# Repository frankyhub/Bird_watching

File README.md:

<div align="center">

|[:skull:ISSUE](https://github.com/frankyhub/Bird_watching/issues?q=is%3Aissue)|[:speech_balloon: Forum /Discussion](https://github.com/frankyhub/Bird_watching/discussions)|[:grey_question:WiKi](https://github.com/frankyhub/Bird_watching/wiki)||
|--|--|--|--|
| | | | |
<a href="https://github.com/frankyhub/Bird_watching/issues">|<a href="https://github.com/frankyhub/Bird_watching/discussions">|<a href="https://github.com/frankyhub/Bird_watching/releases">||
|| <a href="https://github.com/frankyhub/Bird_watching/pulse" alt="Activity">| <a href="https://github.com/frankyhub/Bird_watching/graphs/traffic">  |<a href="https://github.com/frankyhub?tab=stars"> ||

</div>

### Nach einer Idee von [Alex Kutschera](https://github.com/vektorious)

# Story
Die Blaumeise und die Kohlmeise gehören zu den häufigsten Meisenarten in Deutschland. Sie gehen nicht nur gerne an Futterhäuschen, sondern suchen auch Nistkästen auf, in denen sie Schutz suchen und ihre Familie gründen können. Für jede Vogelart gibt es eine ideale Größe des Einfluglochs. Bei den kleinen Blaumeisen sind das 28 Millimeter Durchmesser, bei den größeren Kohlmeisen 32 und beim Star 45mm Lochgröße. Die Lightburnvorlage ist für Kohlmeisen ausgelegt.  Das Einflugloch sollte in Richtung Ost / Südost ausgerichtet sein. 

Die Kohlmeise ist ein kleiner Singvogel. Sie hat einen schwarzen Kopf, weiße Wangen und gelbes Gefieder an Brust und Bauch, sie sind etwa 11 bis 12 Zentimeter groß und wiegen zwischen 9 und 12 Gramm. Mit der CAM des ESP32 und dem WEB-Server kann man in den Nistkasten das Schlüpfen der Jungvögel beobachten. Die 4 IR-LEDs lassen sich über den WEB-Server ein/aus schalten. Der WEB-Server hat eine feste IP-Adresse: 192.160.0.177. Um den WiFi-Empfang des ESP zu verbessern, wurde die Antenne des ESP32-CAM mit 40cm Litze verlängert. In der Testphase ist mit dem Serielllen Monitor die WiFi-Verbindung und die Schaltvorgänge der IR-LEDs zu kontrollieren. Für die Spannungsversorgung ist ein 5V-Netzteil vorgesehen. Möglich ist auch eine Spannungsversorgung mit einem 18650 Akku, der von einem Solor-Panel gespeist wird.

---

### Der WEB-Server:

<br> <br>

---

### Serieller Monitor:

<br> <br>

---

### BOM

| Stück | Bezeichnung |
| ----- | ----------- | 
| 1        | ESP32 CAM      | 
| 1        | ESP32 CAM Shield    | 
| 4        | IR-LEDs 850 nm DC 1,5V 20mA   | 
| 4        | 75R 1/4W  | 
| 1        | 10cm Blankdraht  | 
| 1        | 40cm Litze für die Wurfantenne  | 
| 1        | Schaltdraht      |
| 1        | 5V Netzteil |
| 1        | Vogelhaus: |
| 2        | Sperrholz 4mm 300x600 |
| ----- | ----------- | 

---

[Bauanleitung](https://github.com/frankyhub/Bird_watching/wiki)

---

### Birdhouse aus dem Lasercutter:

<br> <br>

### CAM-Bild

<br> <br>

### Verdrahtung des ESP32-CAM und der IR-LEDs

<br> <br>

<br> <br>

---

<div style="position:absolute; left:2cm; ">   
<ol class="breadcrumb" style="border-top: 2px solid black;border-bottom:2px solid black; height: 45px; width: 900px;"> <p align="center"><a href="#oben">nach oben</a></p></ol>
</div>

---

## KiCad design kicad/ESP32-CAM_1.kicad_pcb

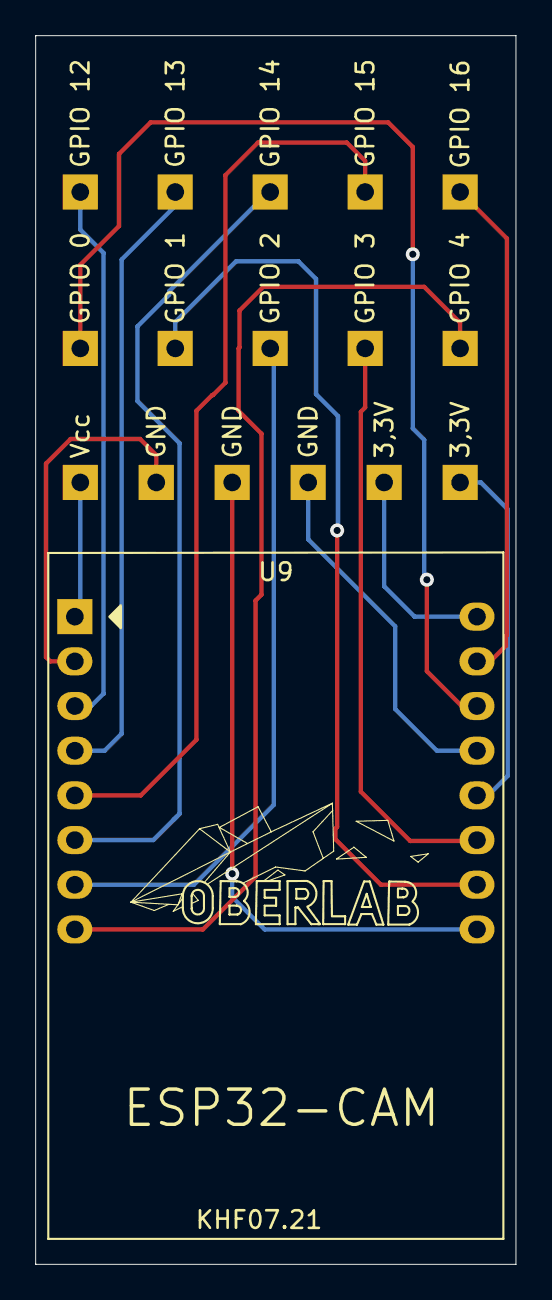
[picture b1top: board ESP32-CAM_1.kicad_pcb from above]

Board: 2 copper layers, 27.3 x 69.8 mm, 17 parts (0 on the bottom side), 16 nets.

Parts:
3,3V, 3,3V#2: LP
GND: LP
GND#2, GND#3: LP
GPIO 0, GPIO 1, GPIO 2, GPIO 3, GPIO 4, GPIO 12, GPIO 13, GPIO 14, GPIO 15, GPIO 16: LP
U9: ESP32-CAM
Vcc: LP

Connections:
unnamed: U9.1, Vcc.1
unnamed: GND.1, U9.2
unnamed: GPIO 12.1, U9.3
unnamed: GPIO 13.1, U9.4
unnamed: GPIO 15.1, U9.5
unnamed: GPIO 14.1, U9.6
unnamed: GPIO 2.1, U9.7
unnamed: GPIO 4.1, U9.8
unnamed: 3,3V.1, U9.16
unnamed: GPIO 16.1, U9.15
unnamed: GPIO 0.1, U9.14
unnamed: GND#2.1, U9.13
unnamed: 3,3V#2.1, U9.12
unnamed: GPIO 3.1, U9.11
unnamed: GPIO 1.1, U9.10
unnamed: GND#3.1, U9.9

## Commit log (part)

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2024-03-08 V1.1 08.03.2024
2024-03-09 Netzteil Update README.md
2024-03-09 V1.2 09.03.2024
2024-03-10 Sperrholz
2024-03-10 V1.0 10.03.2024
2024-03-10 Bauanleitung
2024-03-10 Shield
2024-03-10 V1.1 10.03.2024 Einstiegshilfe
2024-03-10 IR-LED Update README.md
2024-03-10 V1.1 10.03.2024 IR-LED
2024-03-10 V1.0 10.03.2024 Dach
2024-03-10 180R Update README.md
2024-03-10 Story Update README.md
2024-03-10 Kohlmeise Update README.md
2024-03-10 V1.3 10.03.2024
2024-03-10 V1.2 10.03.2024
2024-03-10 V1.3 8mm Cam 10.03.2024
2024-03-10 V1,0 ESP-Spacer 10.03.2024
2024-03-10 V1 10.03.2024
2024-03-10 V1,1 10.03.2024
2024-03-11 V1.0 11.03.2024
2024-03-11 Birdhouse1 Update README.md
2024-03-11 Birdhouse 1 Update README.md
2024-03-12 V1.1 12.03.2024
2024-03-23 V1.4 23.03.2024 IR-LED, Antenne
2024-03-23 V1.4 23.04.2024 IR-LED, Antenne
2024-03-23 V1.1 24.03.2024
2024-03-23 V1.2 23.03.2024 IR-LED
2024-03-23 V1.0 23.03.2024 Funktionstest
2024-03-23 V1-0 23.03.2024
2024-03-24 V1.0 24.03.2024
2024-03-24 V1.5 24.03.2024 IR-LED, 5V, Antenne
2024-03-24 V1.5 24.03.2024 IR-LED, 5V, Antenne
2024-10-12 V12102024
